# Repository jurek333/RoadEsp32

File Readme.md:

# RoadEsp32

Implementacja własnego RoadBook'a na ESP32 S3/C3, LCD 240x280 (ST7789V2), SPI SdCard, I2C GNSS, I2C ekspander do obsługi potencjalnie kliku przycisków (obecnie myślę bazować na 2-ch).

## Sterowanie
Przy ograniczonej ilości przycisków możliwych do obsługi kciukiem, dostawionych do manetki przy lewej ręce, stawiam na 2 przyciski: następny, poprzedni, oba przyciśnięte ok 1s (akceptacja/wyjście).

## Trasy
Tras będą przynajmniej początkowo plikami zawierającymi json z określoną strukturą która dopiero się definiuje. Wszystkie trasy powinny się znajdować na karcie SD w folderze `routes`. Na razie nie implementuje obsługi struktury podfolderów - acz może to być przydatne w przyszłości.

### Stan

Większość kodu to sklejanka PoC "na szybko" by przetestować komponenty i możliwości komunikacji z nimi.

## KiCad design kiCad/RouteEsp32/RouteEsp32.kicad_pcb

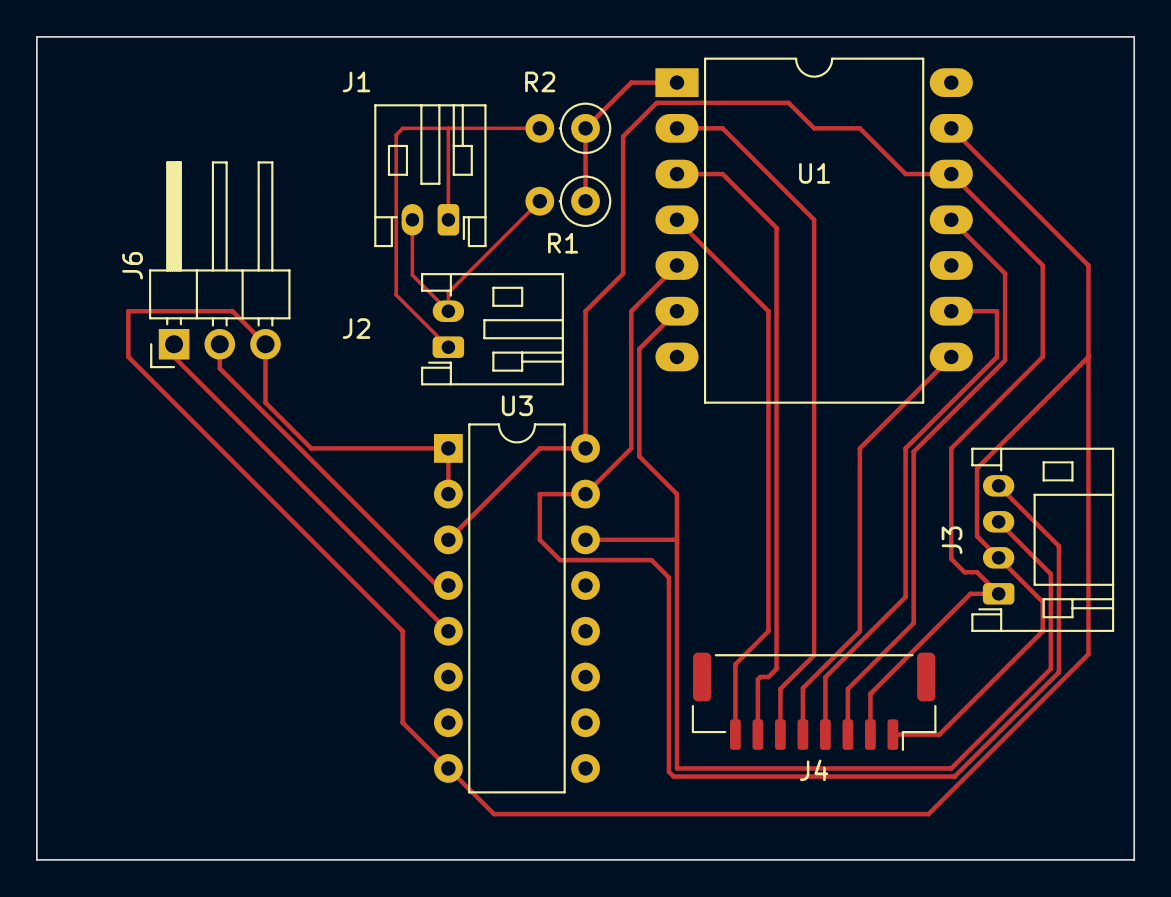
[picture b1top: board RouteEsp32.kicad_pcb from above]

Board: 2 copper layers, 61.0 x 45.7 mm, 9 parts (0 on the bottom side), 15 nets.

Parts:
J1: BAT; JST_PH_S2B-PH-K_1x02_P2.00mm_Horizontal
J2: ESP32 BAT; JST_PH_S2B-PH-K_1x02_P2.00mm_Horizontal
J3: GNSS I2C; JST_PH_S4B-PH-K_1x04_P2.00mm_Horizontal
J4: LCD; JST_GH_SM08B-GHS-TB_1x08-1MP_P1.25mm_Horizontal
J6: BTNS; PinHeader_1x03_P2.54mm_Horizontal
R1, R2: R; R_Axial_DIN0207_L6.3mm_D2.5mm_P2.54mm_Vertical
U1: XIAO ESP32S3; DIP-14_W15.24mm_LongPads
U3: PCF8574; DIP-16_W7.62mm

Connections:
+3V3: J3.1, J4.2, U1.12 (3V3), U3.3 (A2), U3.16 (VDD)
/+: J1.1, J2.1, R2.2
/-: J1.2, J2.2, R1.2
/Btn1: J6.1, U3.5 (P1)
/Btn2: J6.2, U3.4 (P0)
/LCD_CS: J4.5, U1.8 (PB09_D7_RX)
/MOSI: J4.3, U1.11 (PA6_A10_D10_MOSI)
/SCK: J4.4, U1.9 (PA7_A8_D8_SCK)
/SCL: J3.3, U1.6 (PA9_A5_D5_SCL), U3.14 (SCL)
/SDA: J3.4, U1.5 (PA8_A4_D4_SDA), U3.15 (SDA)
BatLvl: R1.1, R2.1, U1.1 (PA02_A0_D0)
GND: J3.2, J4.1, J6.3, U1.13 (GND), U3.1 (A0), U3.2 (A1), U3.8 (VSS)
LCD_BL: J4.8, U1.4 (PA11_A3_D3)
LCD_DC: J4.6, U1.2 (PA4_A1_D1)
LCD_RS: J4.7, U1.3 (PA10_A2_D2)

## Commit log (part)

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2024-05-13 PoC mess
2024-05-13 add readme
2024-05-13 license
2024-05-18 cleanup, extract smallbuffers
2024-05-18 fix a typo after renaming init->Init
2024-05-19 fix navi screen, add windows class
2024-05-25 add UT for parser, exclude state machine, etc
2024-05-25 remove dot folders
2024-05-25 add dot folder s to gitignore
2024-05-26 split json parser and route reader, new UT
2024-05-27 UT and some schema for PCB
2024-05-27 read directions on navigation screen - crude PoC
2024-05-27 create vector during reading and handle prev btn
2024-05-31 fix route direction, extend font by polish chars
2024-06-07 extract new level for lcd, change images, add gps screen
